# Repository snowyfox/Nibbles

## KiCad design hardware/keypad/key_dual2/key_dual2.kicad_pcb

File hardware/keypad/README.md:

# Keypad boards

Physical buttons for the base station, replacing the 3.49's touch screen as
the main input (see `firmware/base/`). Small 2-layer boards, made by
`tools/hardware/make_keypad_kicad.py` (run with KiCad's Python; see its
header). Once a board has been edited in KiCad, edit it there, not by
rerunning the script, which overwrites the project.

Since 2026-11-08 the key boards **daisy-chain**: each has an IN (J1) and an
OUT (J2) connector and its own 5 V buffer for the LED data, so no hub is
needed. key_dual2 (2026-11-08) is key_column_chain's routed board twice over:
column B is the same layout 18 mm to the right (16 mm would overlap the copper
along the column edges), references + 100 and nets suffixed `_B` (GND shared).
Chain A's J2 to B's J101 with a short GH8 cable; set B's address with JP101
(cut to 2-3 for 0x39). key_upper and key_column_chain are routed and DRC clean apart from
silkscreen. **key_dual is not finished:** autorouted (Freerouting) and cleared
of edge-clearance errors, but KEY15's pull-up (RN4 pin 3), column A's +5V chain
to the main +5V, and GND stitching for a few back-pour islands (6 starved
thermals) are still open; DRC lists them as unconnected.

| Project | What | Size |
|---|---|---|
| `key_dual2/` | 16 keys: two complete key_column_chain columns side by side, 18 mm apart, each with its own J1/J2 (B: J101/J102); routed, DRC clean apart from silkscreen | 36 x 168.2 mm |
| `key_dual/` | 16 keys at 16 mm both ways, two TCA9534As, one J1/J2: not finished (see below) | 36 x 160.4 mm |
| `key_upper/` | 3 keys in one column, for the top of the pole's bottom segment, daisy chain | 18 x 88.2 mm |
| `key_column_chain/` | 8 keys in one column, daisy chain | 18 x 168.2 mm |
| `key_column/` | 8 keys in one column, the earlier hub version (one connector), kept as it was | 18 x 156.2 mm |
| `key_hub/` | the earlier hub: power board keypad port out to 4 hub-version boards | 48 x 24 mm |

`nibbles_keys.pretty` holds the hotswap socket footprint, shared by the key
boards. Everything else is KiCad's own library.

## How it connects

```
power board J9 (GH6) ─┐
3.49 GPIO 43 (wire) ──┴─ J1 key_dual J2 ── J1 key_upper J2 ── (J1 of a further board)
```

Every chain board has the same **JST-GH 8** pinout on J1 (in) and J2 (out),
wired straight through: 1 GND, 2 +3V3, 3 SDA, 4 SCL, 5 INT, 6 +5V, 7 LED
data (in on J1, out on J2), 8 unused. Pins 1-6 are the power board's GH6
keypad pinout (J9, J11). Plain straight-through GH8 cables link the boards;
the order of the boards sets the order of the LEDs.

- **The cable from the power board** is J9's GH6 plus one wire from the
  3.49's GPIO 43, on the first board's J1 pin 7. GPIO 43 is free (UART0 TX; the base's
  console is on USB, and the dock UART only uses GPIO 44 to receive). On the
  power board it's J6 pad B5, which isn't connected: solder the wire to that
  header pin's tail on the bottom, or to the 3.49's own hole if using J10.
  J11 stays spare.
- **Keys:** each TCA9534A (one per column; key_dual has two) reads its keys (pressed = low; 10k
  pull-ups, since the TCA9534A has none) and pulls the shared INT low on
  any change. Addresses 0x38-0x3F (A0-A2 on JP1-JP3, bridged to 0 as made;
  cut 1-2 and bridge 2-3 for a 1), clear of the power board's TCA9534 at
  0x20, the INA226 at 0x40 and the BQ25798 at 0x6B. Give every expander its
  own address: key_dual's U2 uses JP4-JP6, so cut JP4 to 2-3 for 0x39, and
  key_upper then needs e.g. 0x3A (cut its JP2 to 2-3). The I2C and INT
  pull-ups are on the power board.
- **LEDs:** SK6812MINI-E (RGB, reverse mount: soldered on the back, shining
  through a hole into the switch's LED window). Each board's 74AHCT1G125
  (U3, with a 100k pull-down on its input) buffers the data from J1 pin 7
  to 5 V, through 100 ohm into the first LED; the last LED drives J2 pin 7
  through 100 ohm. On key_dual the data runs down column A, then down
  column B, so LED order = key order. The firmware caps the total
  brightness: 19 LEDs at full white would draw over 1 A from the 5 V on the
  GH cables.

## Key boards

- **Kailh Box Navy** switches (MX pins) in **Kailh CPG151101S11 hotswap
  sockets** on the back, 16 mm pitch (key_dual: 16 mm both ways). Box housings are
  15.6 mm square, so a 14 mm plate cutout leaves a 2 mm web between keys.
  No keycaps assumed: the custom rockers press the stems directly.
- The LED sits on the switch's LED-window side, opposite the two metal
  pins (checked on a real Box Navy, 2026-10-29).
- Everything is on the back: one-sided assembly, hand-solderable (0603,
  TSSOP-16, the LED's 4 pads). The front only has the switch holes.
- M2 holes at both ends.
- Routing (laid out by hand on `key_upper`): everything on the back, GND
  pours on both sides. KEY1-3 and the LED data in run down the **back's
  right edge** (only four lanes fit past the socket pads). `key_column` is
  `key_upper`'s layout copied key by key, with the electronics 80 mm lower
  (a scratch script, 2026-11-02); its KEY4-8 lines leave each socket pad
  by a via and run down the **front's right edge** in 0.15 mm lanes
  (four of them squeeze between SW8's hole and D8's window), round the
  west end of the front +5V trace and back through vias under U1's
  KEY5-8 pins; KEY4 drops beside U1 pin 7.
- The chain parts (2026-11-08): on key_upper and key_column_chain, J2, U3
  and its resistors and capacitor sit in a strip below J1, 12 mm longer
  than before; the user's routing is kept, apart from the old LED data
  into J1 and one corner of LED_LAST (moved right to let LED_IN out of
  J1 pin 7). key_dual's per-key LED and 5 V wiring is key_column's, copied
  key by key into both columns; the rest of key_dual, and the new
  connections on the other two, were routed with Freerouting 2.1.0 and
  finished by hand (scripts in the session, not kept). key_dual is 1 mm wider
  each side than the generator first made it (36 mm), for the KEY lines along
  its edges, and two GND stitching vias near D1 and D9 moved up 0.15 mm.

## Parts (LCSC, in stock 2026-10-28)

| Part | LCSC |
|---|---|
| TCA9534APWR | C206010 |
| SK6812MINI-E | C5149201 |
| Kailh CPG151101S11 hotswap socket | C41430893 |
| JST BM08B-GHS-TBT (GH8 vertical) | C133062 |
| 10k x4 array 0603 (4D03WGJ0103T5E) | C29718 |
| SN74AHCT1G125DBVR (one per chain board) | C7484 |
| 100 nF 0603 / 10 uF 0805 / 22 uF 0805 | C14663 / C15850 / C45783 |
| 100R / 100k 0603 | C22775 / C25803 |

## Checks

ERC clean and the schematic matches the board (DRC's parity check) for all
of them. DRC is clean on the hub; on the key boards it still lists silkscreen
clipped by solder mask, which the fab trims. The board edge clearance is 0.2 mm: KiCad's own
SK6812MINI-E footprint puts its pads 0.25 mm from its cutout.

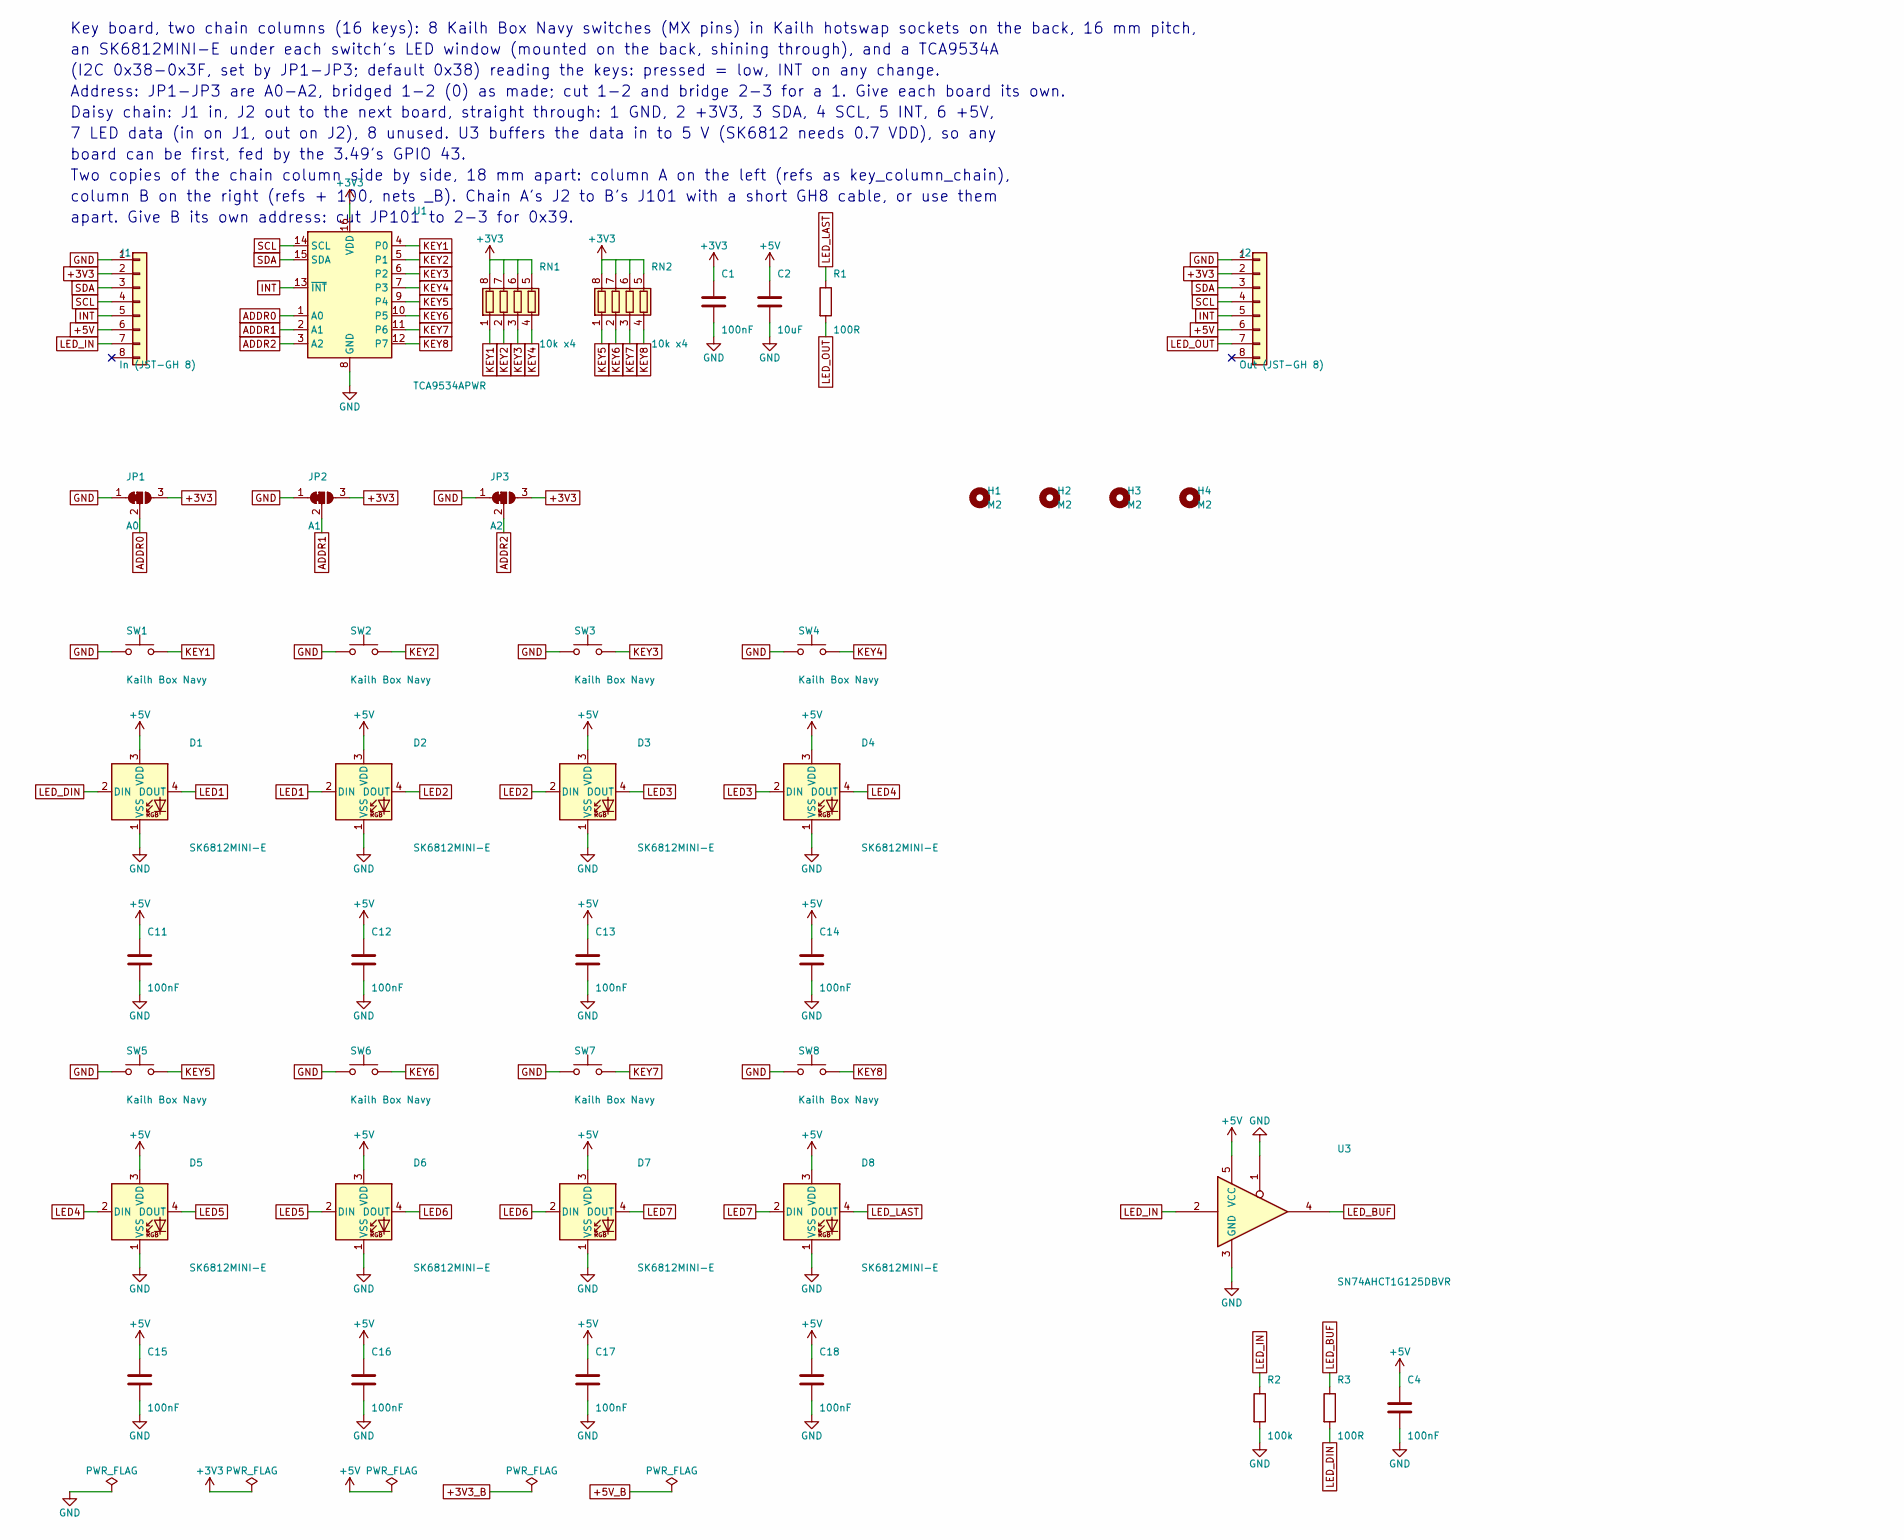
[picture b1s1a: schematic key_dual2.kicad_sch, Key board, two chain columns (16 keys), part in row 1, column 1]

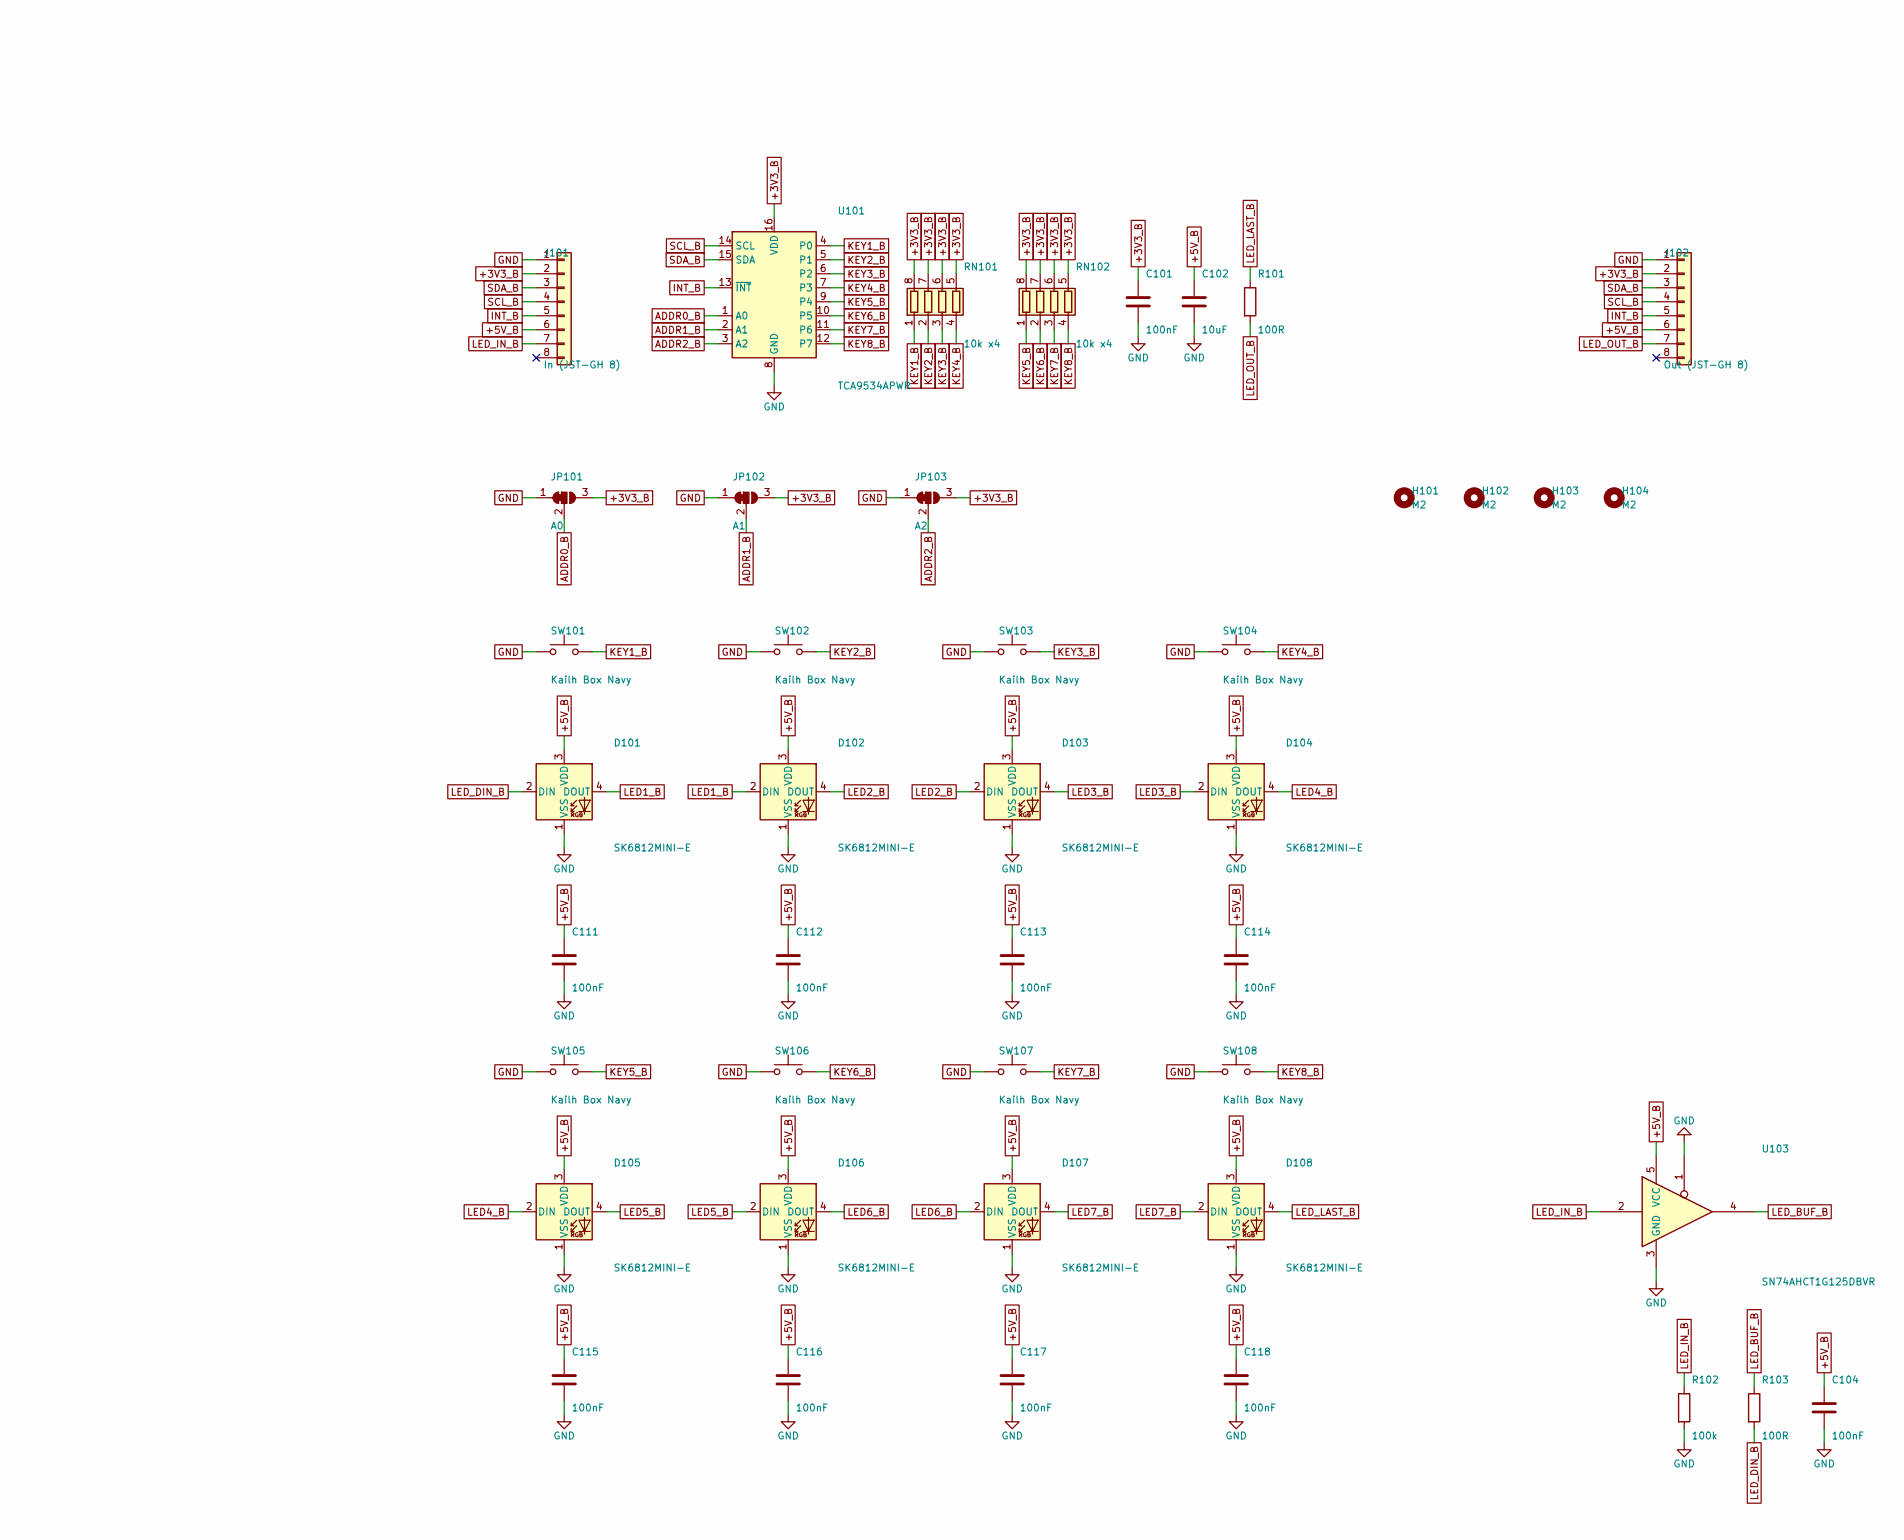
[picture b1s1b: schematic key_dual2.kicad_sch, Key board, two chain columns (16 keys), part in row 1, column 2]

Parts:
C1, C4, C11, C12, C13, C14, C15, C16, C17, C18, C101, C104, C111, C112, C113, C114, C115, C116, C117, C118: 100nF; C_0603_1608Metric; LCSC C14663
C2, C102: 10uF; C_0805_2012Metric; LCSC C15850
D1, D2, D3, D4, D5, D6, D7, D8, D101, D102, D103, D104, D105, D106, D107, D108: SK6812MINI-E; LED_SK6812MINI-E_3.2x2.8mm_P1.5mm_ReverseMount; MPN SK6812MINI-E; LCSC C5149201
H1, H2, H3, H4, H101, H102, H103, H104: M2; MountingHole_2.2mm_M2
J1, J101: In (JST-GH 8); JST_GH_BM08B-GHS-TBT_1x08-1MP_P1.25mm_Vertical; MPN BM08B-GHS-TBT; LCSC C133062
J2, J102: Out (JST-GH 8); JST_GH_BM08B-GHS-TBT_1x08-1MP_P1.25mm_Vertical; MPN BM08B-GHS-TBT; LCSC C133062
JP1, JP101: A0; SolderJumper-3_P1.3mm_Bridged12_RoundedPad1.0x1.5mm_NumberL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
JP2, JP102: A1; SolderJumper-3_P1.3mm_Bridged12_RoundedPad1.0x1.5mm_NumberL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
JP3, JP103: A2; SolderJumper-3_P1.3mm_Bridged12_RoundedPad1.0x1.5mm_NumberL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
R1, R3, R101, R103: 100R; R_0603_1608Metric; LCSC C22775
R2, R102: 100k; R_0603_1608Metric; LCSC C25803
RN1, RN2, RN101, RN102: 10k x4; R_Array_Convex_4x0603; MPN 4D03WGJ0103T5E; LCSC C29718
SW1, SW2, SW3, SW4, SW5, SW6, SW7, SW8, SW101, SW102, SW103, SW104, SW105, SW106, SW107, SW108: Kailh Box Navy; SW_Kailh_MX_Hotswap; MPN Kailh CPG151101S11 socket; LCSC C41430893
U1, U101: TCA9534APWR; TSSOP-16_4.4x5mm_P0.65mm; MPN TCA9534APWR; LCSC C206010
U3, U103: SN74AHCT1G125DBVR; SOT-23-5; MPN SN74AHCT1G125DBVR; LCSC C7484

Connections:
+3V3: C1.1, J1.2, J2.2, JP1.3 (B), JP2.3 (B), JP3.3 (B), RN1.5 (R4.2), RN1.6 (R3.2), RN1.7 (R2.2), RN1.8 (R1.2), RN2.5 (R4.2), RN2.6 (R3.2), RN2.7 (R2.2), RN2.8 (R1.2), U1.16 (VDD)
+3V3_B: C101.1, J101.2, J102.2, JP101.3 (B), JP102.3 (B), JP103.3 (B), RN101.5 (R4.2), RN101.6 (R3.2), RN101.7 (R2.2), RN101.8 (R1.2), RN102.5 (R4.2), RN102.6 (R3.2), RN102.7 (R2.2), RN102.8 (R1.2), U101.16 (VDD)
+5V: C2.1, C4.1, C11.1, C12.1, C13.1, C14.1, C15.1, C16.1, C17.1, C18.1, D1.3 (VDD), D2.3 (VDD), D3.3 (VDD), D4.3 (VDD), D5.3 (VDD), D6.3 (VDD), D7.3 (VDD), D8.3 (VDD), J1.6, J2.6, U3.5 (VCC)
+5V_B: C102.1, C104.1, C111.1, C112.1, C113.1, C114.1, C115.1, C116.1, C117.1, C118.1, D101.3 (VDD), D102.3 (VDD), D103.3 (VDD), D104.3 (VDD), D105.3 (VDD), D106.3 (VDD), D107.3 (VDD), D108.3 (VDD), J101.6, J102.6, U103.5 (VCC)
ADDR0: JP1.2 (C), U1.1 (A0)
ADDR0_B: JP101.2 (C), U101.1 (A0)
ADDR1: JP2.2 (C), U1.2 (A1)
ADDR1_B: JP102.2 (C), U101.2 (A1)
ADDR2: JP3.2 (C), U1.3 (A2)
ADDR2_B: JP103.2 (C), U101.3 (A2)
GND: C1.2, C2.2, C4.2, C11.2, C12.2, C13.2, C14.2, C15.2, C16.2, C17.2, C18.2, C101.2, C102.2, C104.2, C111.2, C112.2, C113.2, C114.2, C115.2, C116.2, C117.2, C118.2, D1.1 (VSS), D2.1 (VSS), D3.1 (VSS), D4.1 (VSS), D5.1 (VSS), D6.1 (VSS), D7.1 (VSS), D8.1 (VSS), D101.1 (VSS), D102.1 (VSS), D103.1 (VSS), D104.1 (VSS), D105.1 (VSS), D106.1 (VSS), D107.1 (VSS), D108.1 (VSS), J1.1, J2.1, J101.1, J102.1, JP1.1 (A), JP2.1 (A), JP3.1 (A), JP101.1 (A), JP102.1 (A), JP103.1 (A), R2.2, R102.2, SW1.1, SW2.1, SW3.1, SW4.1, SW5.1, SW6.1, SW7.1, SW8.1, SW101.1, SW102.1, SW103.1, SW104.1, SW105.1, SW106.1, SW107.1, SW108.1, U1.8 (GND), U3.1, U3.3 (GND), U101.8 (GND), U103.1, U103.3 (GND)
INT: J1.5, J2.5, U1.13 (~INT)
INT_B: J101.5, J102.5, U101.13 (~INT)
KEY1: RN1.1 (R1.1), SW1.2, U1.4 (P0)
KEY1_B: RN101.1 (R1.1), SW101.2, U101.4 (P0)
KEY2: RN1.2 (R2.1), SW2.2, U1.5 (P1)
KEY2_B: RN101.2 (R2.1), SW102.2, U101.5 (P1)
KEY3: RN1.3 (R3.1), SW3.2, U1.6 (P2)
KEY3_B: RN101.3 (R3.1), SW103.2, U101.6 (P2)
KEY4: RN1.4 (R4.1), SW4.2, U1.7 (P3)
KEY4_B: RN101.4 (R4.1), SW104.2, U101.7 (P3)
KEY5: RN2.1 (R1.1), SW5.2, U1.9 (P4)
KEY5_B: RN102.1 (R1.1), SW105.2, U101.9 (P4)
KEY6: RN2.2 (R2.1), SW6.2, U1.10 (P5)
KEY6_B: RN102.2 (R2.1), SW106.2, U101.10 (P5)
KEY7: RN2.3 (R3.1), SW7.2, U1.11 (P6)
KEY7_B: RN102.3 (R3.1), SW107.2, U101.11 (P6)
KEY8: RN2.4 (R4.1), SW8.2, U1.12 (P7)
KEY8_B: RN102.4 (R4.1), SW108.2, U101.12 (P7)
LED1: D1.4 (DOUT), D2.2 (DIN)
LED1_B: D101.4 (DOUT), D102.2 (DIN)
LED2: D2.4 (DOUT), D3.2 (DIN)
LED2_B: D102.4 (DOUT), D103.2 (DIN)
LED3: D3.4 (DOUT), D4.2 (DIN)
LED3_B: D103.4 (DOUT), D104.2 (DIN)
LED4: D4.4 (DOUT), D5.2 (DIN)
LED4_B: D104.4 (DOUT), D105.2 (DIN)
LED5: D5.4 (DOUT), D6.2 (DIN)
LED5_B: D105.4 (DOUT), D106.2 (DIN)
LED6: D6.4 (DOUT), D7.2 (DIN)
LED6_B: D106.4 (DOUT), D107.2 (DIN)
LED7: D7.4 (DOUT), D8.2 (DIN)
LED7_B: D107.4 (DOUT), D108.2 (DIN)
LED_BUF: R3.1, U3.4
LED_BUF_B: R103.1, U103.4
LED_DIN: D1.2 (DIN), R3.2
LED_DIN_B: D101.2 (DIN), R103.2
LED_IN: J1.7, R2.1, U3.2
LED_IN_B: J101.7, R102.1, U103.2
LED_LAST: D8.4 (DOUT), R1.1
LED_LAST_B: D108.4 (DOUT), R101.1
LED_OUT: J2.7, R1.2
LED_OUT_B: J102.7, R101.2
SCL: J1.4, J2.4, U1.14 (SCL)
SCL_B: J101.4, J102.4, U101.14 (SCL)
SDA: J1.3, J2.3, U1.15 (SDA)
SDA_B: J101.3, J102.3, U101.15 (SDA)

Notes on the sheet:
Key board, two chain columns (16 keys): 8 Kailh Box Navy switches (MX pins) in Kailh hotswap sockets on the back, 16 mm pitch,
an SK6812MINI-E under each switch's LED window (mounted on the back, shining through), and a TCA9534A
(I2C 0x38-0x3F, set by JP1-JP3; default 0x38) reading the keys: pressed = low, INT on any change.
Address: JP1-JP3 are A0-A2, bridged 1-2 (0) as made; cut 1-2 and bridge 2-3 for a 1. Give each board its own.
Daisy chain: J1 in, J2 out to the next board, straight through: 1 GND, 2 +3V3, 3 SDA, 4 SCL, 5 INT, 6 +5V,
7 LED data (in on J1, out on J2), 8 unused. U3 buffers the data in to 5 V (SK6812 needs 0.7 VDD), so any
board can be first, fed by the 3.49's GPIO 43.
Two copies of the chain column side by side, 18 mm apart: column A on the left (refs as key_column_chain),
column B on the right (refs + 100, nets _B). Chain A's J2 to B's J101 with a short GH8 cable, or use them
apart. Give B its own address: cut JP101 to 2-3 for 0x39.

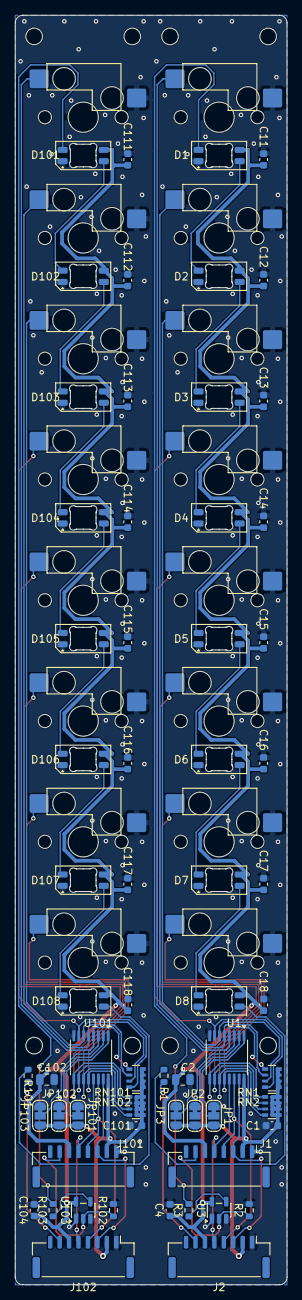
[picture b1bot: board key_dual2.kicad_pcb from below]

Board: 2 copper layers, 36.0 x 168.2 mm, 86 parts (62 on the bottom side), 57 nets.

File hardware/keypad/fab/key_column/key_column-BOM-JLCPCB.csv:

Comment,Designator,Footprint,LCSC Part #
100nF,"C1,C11,C12,C13,C14,C15,C16,C17,C18",C_0603_1608Metric,C14663
10uF,C2,C_0805_2012Metric,C15850
SK6812MINI-E,"D1,D2,D3,D4,D5,D6,D7,D8",LED_SK6812MINI-E_3.2x2.8mm_P1.5mm_ReverseMount,C5149201
Hub (JST-GH 8),J1,JST_GH_BM08B-GHS-TBT_1x08-1MP_P1.25mm_Vertical,C133062
100R,R1,R_0603_1608Metric,C22775
10k x4,"RN1,RN2",R_Array_Convex_4x0603,C29718
Kailh hotswap socket CPG151101S11,"SW1,SW2,SW3,SW4,SW5,SW6,SW7,SW8",SW_Kailh_MX_Hotswap,C41430893
TCA9534APWR,U1,TSSOP-16_4.4x5mm_P0.65mm,C206010

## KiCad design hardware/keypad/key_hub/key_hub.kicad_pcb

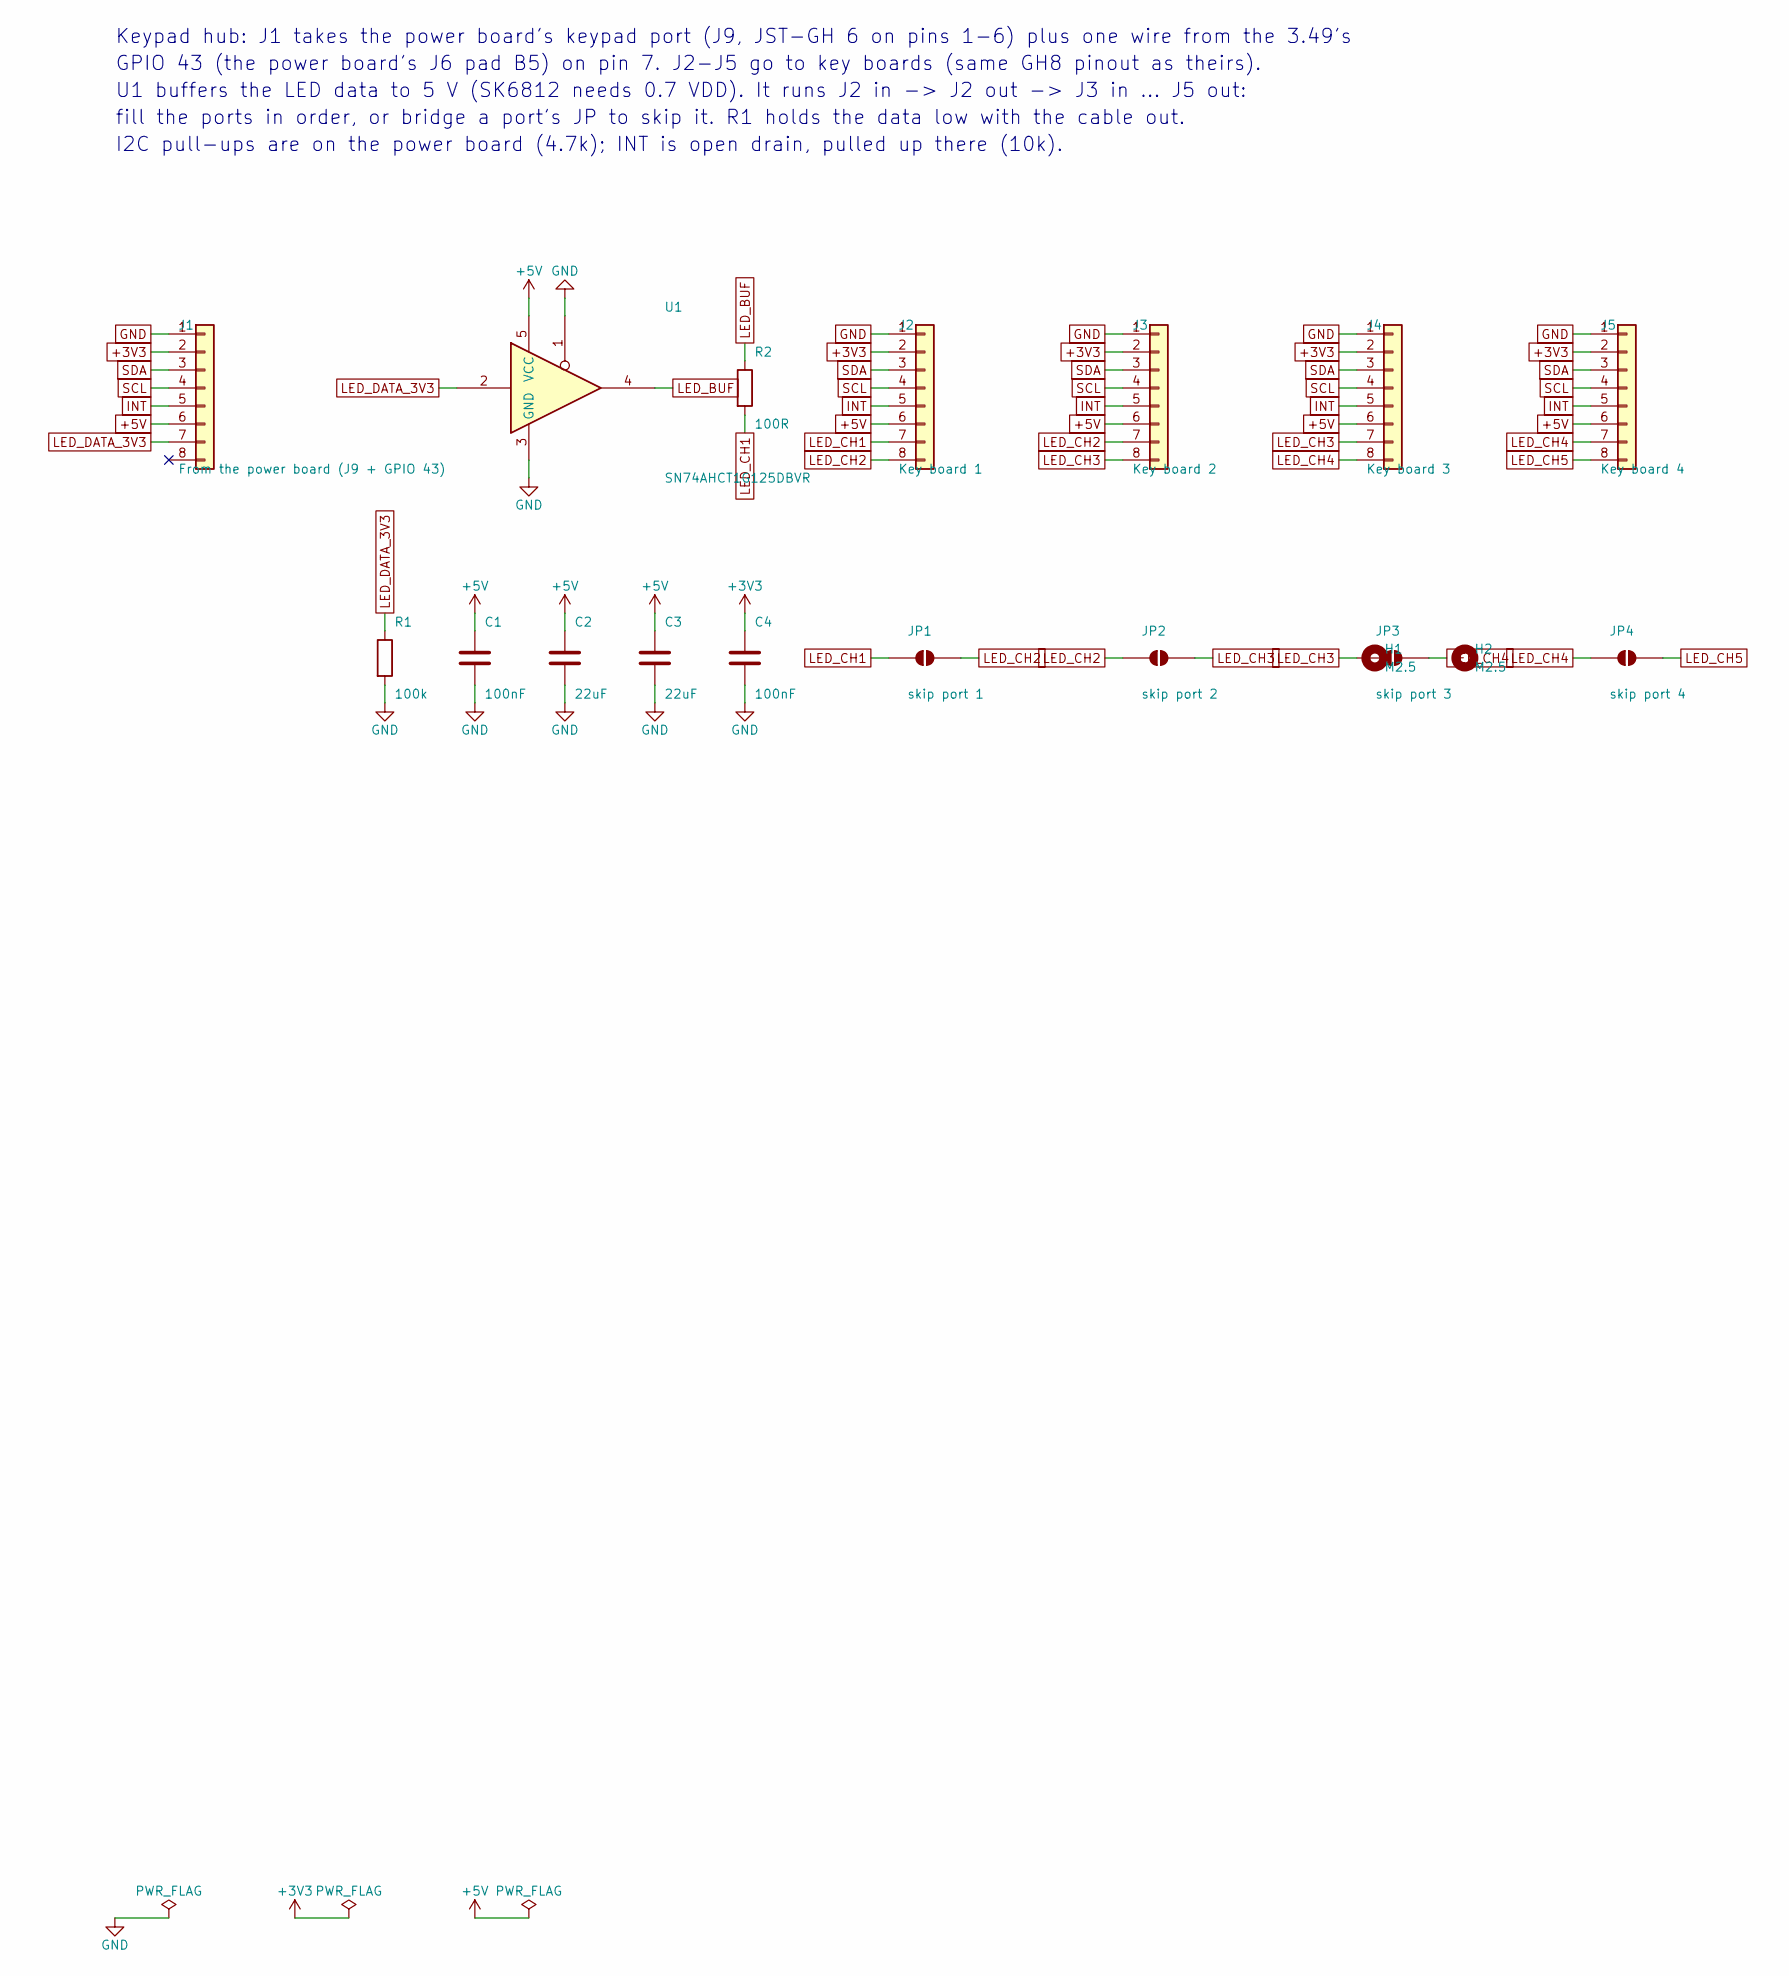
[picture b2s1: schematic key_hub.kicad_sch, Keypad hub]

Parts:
C1, C4: 100nF; C_0603_1608Metric; LCSC C14663
C2, C3: 22uF; C_0805_2012Metric; LCSC C45783
H1, H2: M2.5; MountingHole_2.7mm_M2.5
J1: From the power board (J9 + GPIO 43); JST_GH_BM08B-GHS-TBT_1x08-1MP_P1.25mm_Vertical; MPN BM08B-GHS-TBT; LCSC C133062
J2: Key board 1; JST_GH_BM08B-GHS-TBT_1x08-1MP_P1.25mm_Vertical; MPN BM08B-GHS-TBT; LCSC C133062
J3: Key board 2; JST_GH_BM08B-GHS-TBT_1x08-1MP_P1.25mm_Vertical; MPN BM08B-GHS-TBT; LCSC C133062
J4: Key board 3; JST_GH_BM08B-GHS-TBT_1x08-1MP_P1.25mm_Vertical; MPN BM08B-GHS-TBT; LCSC C133062
J5: Key board 4; JST_GH_BM08B-GHS-TBT_1x08-1MP_P1.25mm_Vertical; MPN BM08B-GHS-TBT; LCSC C133062
JP1: skip port 1; SolderJumper-2_P1.3mm_Open_RoundedPad1.0x1.5mm
JP2: skip port 2; SolderJumper-2_P1.3mm_Open_RoundedPad1.0x1.5mm
JP3: skip port 3; SolderJumper-2_P1.3mm_Open_RoundedPad1.0x1.5mm
JP4: skip port 4; SolderJumper-2_P1.3mm_Open_RoundedPad1.0x1.5mm
R1: 100k; R_0603_1608Metric; LCSC C25803
R2: 100R; R_0603_1608Metric; LCSC C22775
U1: SN74AHCT1G125DBVR; SOT-23-5; MPN SN74AHCT1G125DBVR; LCSC C7484

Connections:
+3V3: C4.1, J1.2, J2.2, J3.2, J4.2, J5.2
+5V: C1.1, C2.1, C3.1, J1.6, J2.6, J3.6, J4.6, J5.6, U1.5 (VCC)
GND: C1.2, C2.2, C3.2, C4.2, J1.1, J2.1, J3.1, J4.1, J5.1, R1.2, U1.1, U1.3 (GND)
INT: J1.5, J2.5, J3.5, J4.5, J5.5
LED_BUF: R2.1, U1.4
LED_CH1: J2.7, JP1.1 (A), R2.2
LED_CH2: J2.8, J3.7, JP1.2 (B), JP2.1 (A)
LED_CH3: J3.8, J4.7, JP2.2 (B), JP3.1 (A)
LED_CH4: J4.8, J5.7, JP3.2 (B), JP4.1 (A)
LED_CH5: J5.8, JP4.2 (B)
LED_DATA_3V3: J1.7, R1.1, U1.2
SCL: J1.4, J2.4, J3.4, J4.4, J5.4
SDA: J1.3, J2.3, J3.3, J4.3, J5.3

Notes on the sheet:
Keypad hub: J1 takes the power board's keypad port (J9, JST-GH 6 on pins 1-6) plus one wire from the 3.49's
GPIO 43 (the power board's J6 pad B5) on pin 7. J2-J5 go to key boards (same GH8 pinout as theirs).
U1 buffers the LED data to 5 V (SK6812 needs 0.7 VDD). It runs J2 in -> J2 out -> J3 in ... J5 out:
fill the ports in order, or bridge a port's JP to skip it. R1 holds the data low with the cable out.
I2C pull-ups are on the power board (4.7k); INT is open drain, pulled up there (10k).

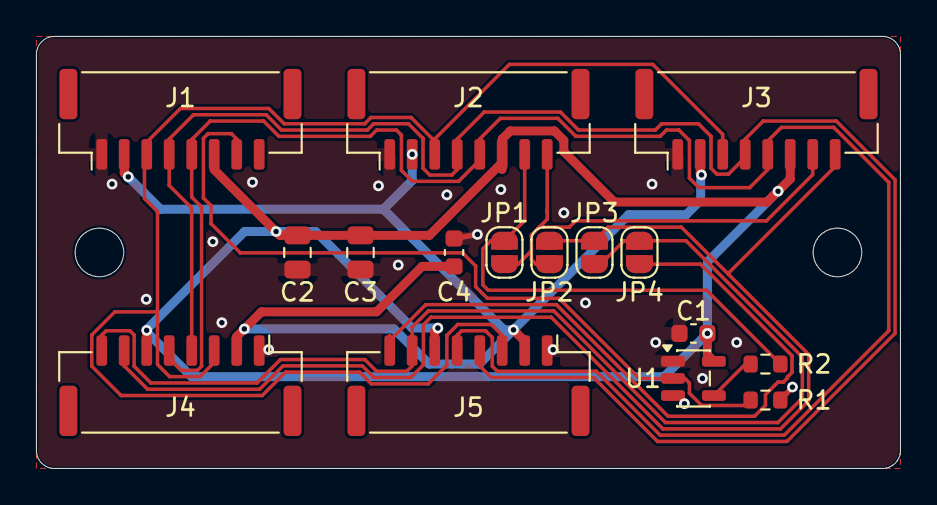
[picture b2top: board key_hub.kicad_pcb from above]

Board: 2 copper layers, 48.0 x 24.0 mm, 18 parts (0 on the bottom side), 13 nets.

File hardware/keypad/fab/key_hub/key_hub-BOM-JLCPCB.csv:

Comment,Designator,Footprint,LCSC Part #
100nF,"C1,C4",C_0603_1608Metric,C14663
22uF,"C2,C3",C_0805_2012Metric,C45783
From the power board (J9 + GPIO 43),"J1,J2,J3,J4,J5",JST_GH_BM08B-GHS-TBT_1x08-1MP_P1.25mm_Vertical,C133062
100k,R1,R_0603_1608Metric,C25803
100R,R2,R_0603_1608Metric,C22775
SN74AHCT1G125DBVR,U1,SOT-23-5,C7484
